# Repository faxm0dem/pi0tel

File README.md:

# 3615 pi0

This uHat is designed to plug on top of a pi0 or pi0-w.
It's designed to plug to the DIN-5 at the back of a Minitel-2.
The pi0 will be powered by the Minitel through the Buck converter on
the hat. TX and RX will be level-shifted to the right level on the pi's UART.

The aim is to plug the resulting dongle into a Minitel, and get instant linux.

3615 pi0 (or shall we say, 31415 Minitel).

# Reference

* https://niteshbharadwaj.github.io/posts/raspi_from_battery.html
* http://pila.fr/wordpress/?p=361
* http://www.jelora.fr/post/2020/02/25/Adaptateur-prise-DIN-peri-informatique-Minitel-vers-Serie-RS232-et-Serie-USB.html
* https://www.ti.com/lit/ds/symlink/lm2596.pdf
* https://www.edn.com/pcb-layout-tips-for-thermal-vias/
* https://www.instructables.com/id/Arduino-to-RPi-three-ways-to-convert-5-volts-to-33/
* https://randomnerdtutorials.com/how-to-level-shift-5v-to-3-3v/

# Notes

* Cin and Cout
  - should both have short leads to lm2596
  - should both have low ESR (e.g. high V rating, Nichicon PL, 1.25*Vin = 10V)
  - Ripple current rating 50% of DC load (500mA in our case)
* Cin 270uF or 330uF
* Cout 470/25 Pana or 560/16 Nichi
* Diode
  - current rating = 1.3*load = 800mA
  - reverse V rating = 1.25*Vinmax = 10V
* Heat pad should at least be 0.4"²
* L choice see page 20 of Datasheet
  - L21/L22

||uH|A|SCHOTT|SCHOTT|RENCO|RENCO|PULSE|PULSE|COILCRAFT|
|-|--|-|------|------|-----|-----|-----|-----|---------|
|L21|68|0.99|67144070|67144450|RL-5471-5|RL1500-68|PE-53821|PE-53821-S|DO3316-683|
|L22|47|1.17|67144080|67144460|RL-5471-6|—|PE-53822|PE-53822-S|DO3316-47|

* If we want low output ripple we can add post ripple filter 1uH-5uH
  with low DC Resistance and low ESR cap

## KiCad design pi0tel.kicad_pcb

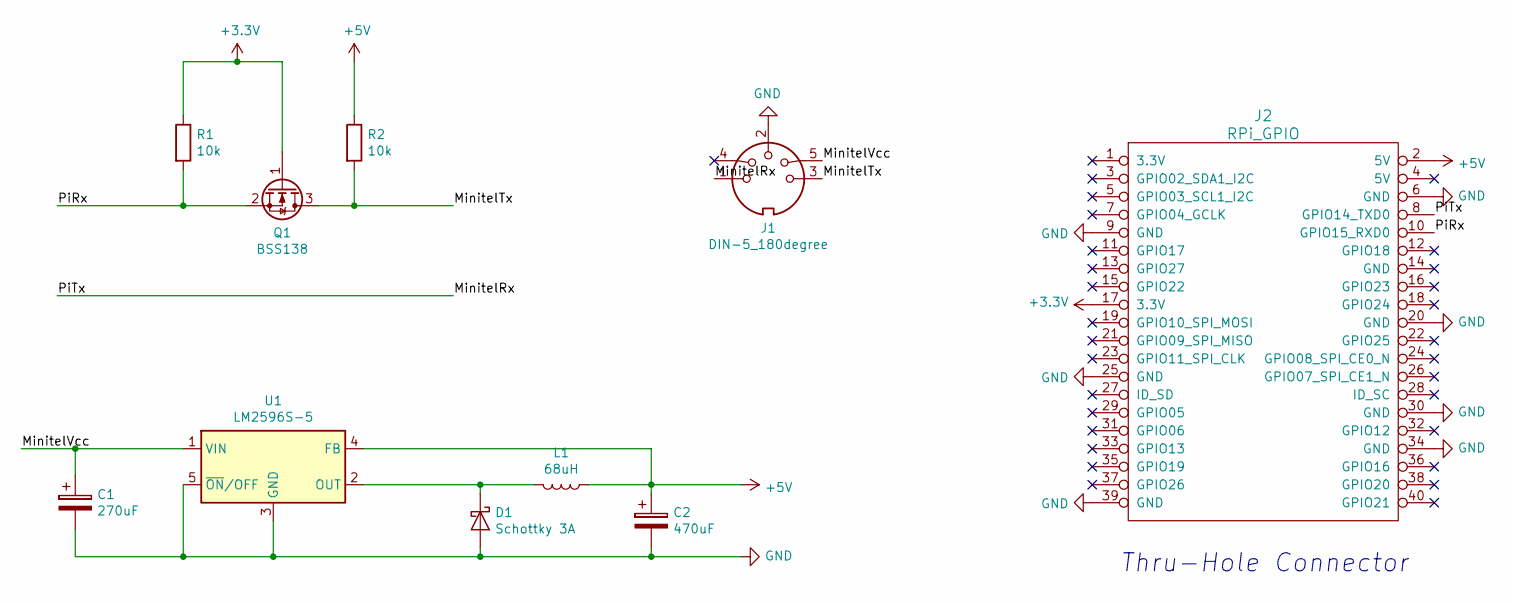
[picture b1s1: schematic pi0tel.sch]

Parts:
C1: 270uF; CP_Elec_8x10.5
C2: 470uF; CP_Elec_8x10.5
D1: Schottky 3A; D_SMA_Handsoldering
J1: DIN-5_180degree; din_5_econet_pcb_mount
J2: RPi_GPIO; PinHeader_2x20_P2.54mm_Vertical
L1: 68uH; L_1210_3225Metric_Pad1.42x2.65mm_HandSolder
Q1: BSS138; SOT-23_Handsoldering
R1, R2: 10k; R_0805_2012Metric_Pad1.15x1.40mm_HandSolder
U1: LM2596S-5; TO-263-5_TabPin3

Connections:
+3V3: J2.17 (3.3V), Q1.1 (G), R1.1
+5V: C2.1, J2.2 (5V), L1.1, R2.1, U1.4 (FB)
/MinitelRx: J1.1, J2.8 (GPIO14_TXD0)
/MinitelTx: J1.3, Q1.3 (D), R2.2
/MinitelVcc: C1.1, J1.5, U1.1 (VIN)
/PiRx: J2.10 (GPIO15_RXD0), Q1.2 (S), R1.2
GND: C1.2, C2.2, D1.2 (A), J1.2, J2.6 (GND), J2.9 (GND), J2.20 (GND), J2.25 (GND), J2.30 (GND), J2.34 (GND), J2.39 (GND), U1.3 (GND), U1.5 (~ON~/OFF)
unnamed: D1.1 (K), L1.2, U1.2 (OUT)

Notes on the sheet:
Thru-Hole Connector

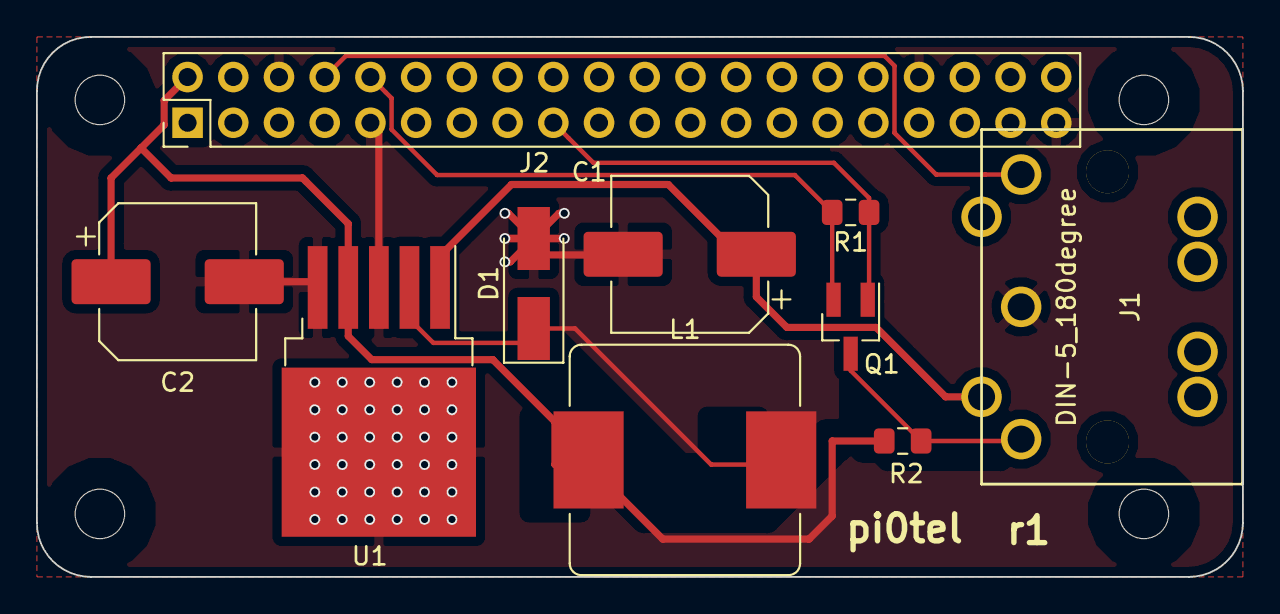
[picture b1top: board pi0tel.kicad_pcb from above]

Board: 2 copper layers, 67.0 x 30.0 mm, 10 parts (0 on the bottom side), 8 nets.

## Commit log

2020-06-28 add stuff
2020-06-29 hmmm
2020-06-29 grrr
2020-06-30 Add research to doc
2020-06-30 Add research
    Thermal considerations on PCB design
2020-06-30 Add references
2020-07-01 getting there
2020-07-01 Remove unnecessary library
2020-07-01 Move din to the back
2020-07-01 Add research to readme
2020-07-01 Add readme
2020-10-22 Move footprints around to match more closely how usual layouts look.
    See for instance
    https://img.gkbcdn.com/s3/p/2015-05-22/lm2596-5v-buck-converter-7-30v-to-5v-step-down-regulator-module-for-diy-project-1571986804286.jpg
2020-10-22 Ground plane
2021-03-13 Put din connector on top side.
    Also a few adjustments
2021-03-13 Increase board size to accomodate for DIN
2021-03-13 Add some text
2021-04-01 Add 3d render
2021-04-11 Fix footprint for Schottky
2021-04-11 Enlarge inductance pads for handsolder
2021-04-11 change inductor again now with 3D model
2021-04-12 Update 3D render
